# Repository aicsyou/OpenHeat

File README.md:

# OpenHeat：开源智能加热台
* 基于[peng-zhihui](https://github.com/peng-zhihui)的[OpenHeat](https://github.com/peng-zhihui/OpenHeat)， 调整了元器件的封装，方便手工焊接
* 项目设计使用KiCAD软件
* 固件不完全兼容（未完成）
* 注意： PCBA测试中

---------------------------------------------------------------------------

> 用于PCB回流焊的实用加热台，比较炫酷，可能目前市面上 **颜值最高** & **功能最强** 的加热台。

**参数：** 硬件方面基于`ESP32PICO-D4`芯片，输入电源`24V/10A`，最大功率200W，加热温度最高300℃；带蓝牙功能，***后续有空的话我会开发手机APP用于设置升温曲线*** 。

## 21-9-17 修复说明：

---

## 关于本项目

* 本项目参考了 [createskyblue](https://gitee.com/createskyblue) / [OpenT12](https://gitee.com/createskyblue/OpenT12)开源T12电烙铁项目的固件，感谢这位同学设计的优秀交互动画体验，UI设计深得我心哈哈~

* 另外铝基板热床的设计采用了[MRobot-Origin](https://github.com/MRobot-Origin)/ [GS_Hbed](https://github.com/MRobot-Origin/GS_Hbed)同学的分型曲线设计，非常有创意~

## 使用说明

#### 1. 打样说明

直接用Hardware文件夹里的Gerber文件打样即可：主控制器为4层PCB，无特殊工艺要求；热床为铝基板PCB，可以在嘉立创打样。

> 铝基板是一种专门用来散热的PCB板材，大家看到的很多大功率LED灯珠就是这种，前阵子嘉立创开放了铝基板打样业务，还很便宜。所以相比于设计一个金属块做热床，这种方式不但成本低而且美观实用。

另外其实还有一块可选两层板作为固定件的，这个我还没来得及设计，也很简单，大家可以根据自己情况画一个，或者直接3D打印结构件固定也行。

#### 2. 固件说明

固件我这边是基于PlatformIO移植的，所以大家用这个平台的话直接打开下载就行了；如果是用Arduino IDE的话，先安装Library里面的库文件，然后一样下载。

固件库没有完全配置完成（因为原版固件是设计为电烙铁使用的），晚些我硬件都就位了会调试好固件供大家直接下载。

#### 3. 关于结构件

这个我也还在设计，我的风格肯定是以美观小巧为主，大家可以等我放出3D打印文件。

#### 4. 关于温度传感器

我这边是用的是K型热电偶，在PCB上已经集成了采集芯片，需要自己买一个表贴式的K型热电偶连接到板子下方的两个焊盘。

> 注意热电偶和热床的接触要绝缘，用高温胶带隔一下就行。另外热电偶是有极性的，如果发现加热后温度反而下降说明接反了。
>
> 现在代码中还没有加热电偶的代码，晚一点有空了会调好完整固件。大家自己添加也很容易，MAX6675使用SPI驱动，Arduino平台有很多例程。

#### 5. 关于元器件BOM

**注意！！！** C9电容一定要选耐压足够的，因为是并联到24V的VCC上，如果耐压不够短路的话可以看到烟花！！

#### 接线图

## 欢迎star支持 :D

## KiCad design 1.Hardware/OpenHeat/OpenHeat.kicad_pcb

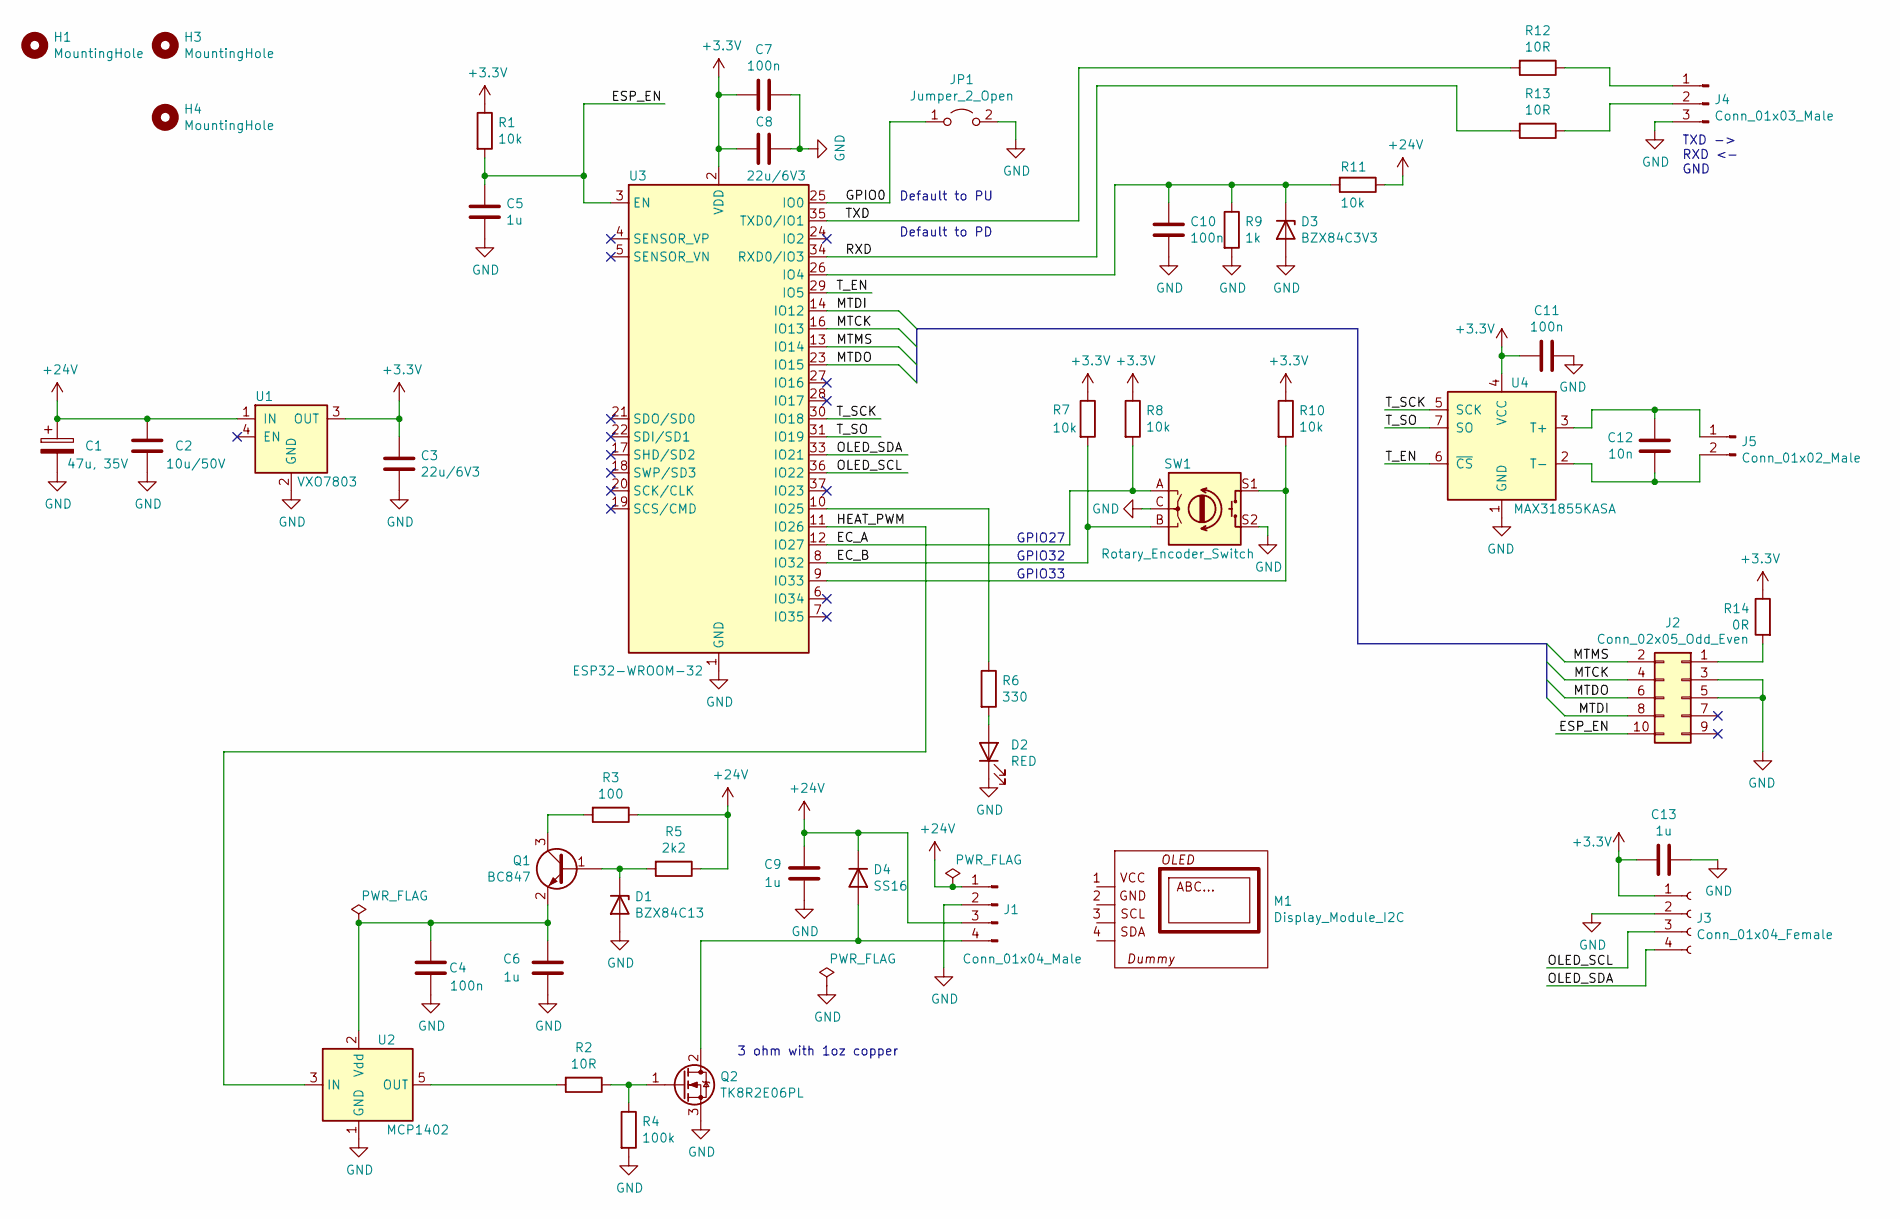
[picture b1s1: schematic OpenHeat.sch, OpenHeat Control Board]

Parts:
C1: 47u, 35V; CP_Radial_D5.0mm_P2.00mm; PartNo 860020472006
C2: 10u/50V; C_1206_3216Metric_Pad1.33x1.80mm_HandSolder
C3, C8: 22u/6V3; C_0805_2012Metric_Pad1.18x1.45mm_HandSolder
C4, C7, C10, C11: 100n; C_0603_1608Metric_Pad1.08x0.95mm_HandSolder
C5, C6, C13: 1u; C_0603_1608Metric_Pad1.08x0.95mm_HandSolder
C9: 1u; C_Rect_L7.2mm_W4.5mm_P5.00mm_FKS2_FKP2_MKS2_MKP2; PartNo B32529C105J
C12: 10n; C_0603_1608Metric_Pad1.08x0.95mm_HandSolder
D1: BZX84C13; D_SOT-23_ANK
D2: RED; LED_0805_2012Metric_Pad1.15x1.40mm_HandSolder
D3: BZX84C3V3; D_SOT-23_ANK
D4: SS16; D_SMA; PartNo SS16_R1_00001
H1, H3, H4: MountingHole; MountingHole_3.2mm_M3
J1: Conn_01x04_Male; TerminalBlock_Phoenix_MKDS-1,5-4-5.08_1x04_P5.08mm_Horizont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
J2: Conn_02x05_Odd_Even; PinHeader_2x05_P1.27mm_Vertical_SMD
J3: Conn_01x04_Female; PinSocket_1x04_P2.54mm_Vertical
J4: Conn_01x03_Male; PinHeader_1x03_P2.54mm_Vertical
J5: Conn_01x02_Male; PinHeader_1x02_P2.54mm_Horizontal
JP1: Jumper_2_Open; PinHeader_1x02_P2.54mm_Vertical
M1: Display_Module_I2C; OLED_128x64_096_I2C
Q1: BC847; SOT-23
Q2: TK8R2E06PL; TO-220-3_Horizontal_TabDown
R1, R7, R8, R10, R11: 10k; R_0603_1608Metric_Pad0.98x0.95mm_HandSolder
R2, R12, R13: 10R; R_0603_1608Metric_Pad0.98x0.95mm_HandSolder
R3: 100; R_0805_2012Metric_Pad1.20x1.40mm_HandSolder
R4: 100k; R_0603_1608Metric_Pad0.98x0.95mm_HandSolder
R5: 2k2; R_0603_1608Metric_Pad0.98x0.95mm_HandSolder
R6: 330; R_0603_1608Metric_Pad0.98x0.95mm_HandSolder
R9: 1k; R_0603_1608Metric_Pad0.98x0.95mm_HandSolder
R14: 0R; R_0603_1608Metric_Pad0.98x0.95mm_HandSolder
SW1: Rotary_Encoder_Switch; RotaryEncoder_Alps_EC11E-Switch_Vertical_H20mm
U1: VXO7803; VXO78-500-M; PartNo VXO7803-500-M-TR
U2: MCP1402; SOT-23-5
U3: ESP32-WROOM-32
U4: MAX31855KASA; SOIC-8_3.9x4.9mm_P1.27mm

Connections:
+3V3: C3.1, C7.1, C8.2, C11.1, C13.2, J3.1, R1.1, R7.1, R8.1, R10.1, R14.1, U1.3 (OUT), U3.2 (VDD), U4.4 (VCC)
+24V: C1.1, C2.1, C9.2, D4.1 (K), J1.1, J1.3, R3.1, R5.1, R11.1, U1.1 (IN)
/EC_A: R8.2, SW1.A, U3.12 (IO27)
/EC_B: R7.2, SW1.B, U3.8 (IO32)
/ESP_EN: C5.1, J2.10, R1.2, U3.3 (EN)
/GPIO0: JP1.1 (A), U3.25 (IO0)
/HEAT_PWM: U2.3 (IN), U3.11 (IO26)
/MTCK: J2.4, U3.16 (IO13)
/MTDI: J2.8, U3.14 (IO12)
/MTDO: J2.6, U3.23 (IO15)
/MTMS: J2.2, U3.13 (IO14)
/OLED_SCL: J3.3, U3.36 (IO22)
/OLED_SDA: J3.4, U3.33 (IO21)
/RXD: R13.2, U3.34 (RXD0/IO3)
/TXD: R12.2, U3.35 (TXD0/IO1)
/T_EN: U3.29 (IO5), U4.6 (~CS~)
/T_SCK: U3.30 (IO18), U4.5 (SCK)
/T_SO: U3.31 (IO19), U4.7 (SO)
GND: C1.2, C2.2, C3.2, C4.2, C5.2, C6.2, C7.2, C8.1, C9.1, C10.2, C11.2, C13.1, D1.2 (A), D2.1 (K), D3.2 (A), J1.2, J2.3, J2.5, J3.2, J4.3, JP1.2 (B), Q2.3 (S), R4.2, R9.2, SW1.C, SW1.S2, U1.2 (GND), U2.1 (GND), U2.4 (GND), U3.1 (GND), U3.15 (GND), U3.38 (GND), U3.39 (GND), U4.1 (GND)
unnamed: C4.1, C6.1, Q1.2 (E), U2.2 (Vdd)
unnamed: C10.1, D3.1 (K), R9.1, R11.2, U3.26 (IO4)
unnamed: C12.1, J5.2, U4.2 (T-)
unnamed: C12.2, J5.1, U4.3 (T+)
unnamed: D1.1 (K), Q1.1 (B), R5.2
unnamed: D2.2 (A), R6.2
unnamed: D4.2 (A), J1.4, Q2.2 (D)
unnamed: J2.1, R14.2
unnamed: J4.1, R12.1
unnamed: J4.2, R13.1
unnamed: Q1.3 (C), R3.2
unnamed: Q2.1 (G), R2.1, R4.1
unnamed: R2.2, U2.5 (OUT)
unnamed: R6.1, U3.10 (IO25)
unnamed: R10.2, SW1.S1, U3.9 (IO33)

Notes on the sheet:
Default to PD
Default to PU
GPIO32
GPIO27
GPIO33
3 ohm with 1oz copper
TXD -> RXD <- GND

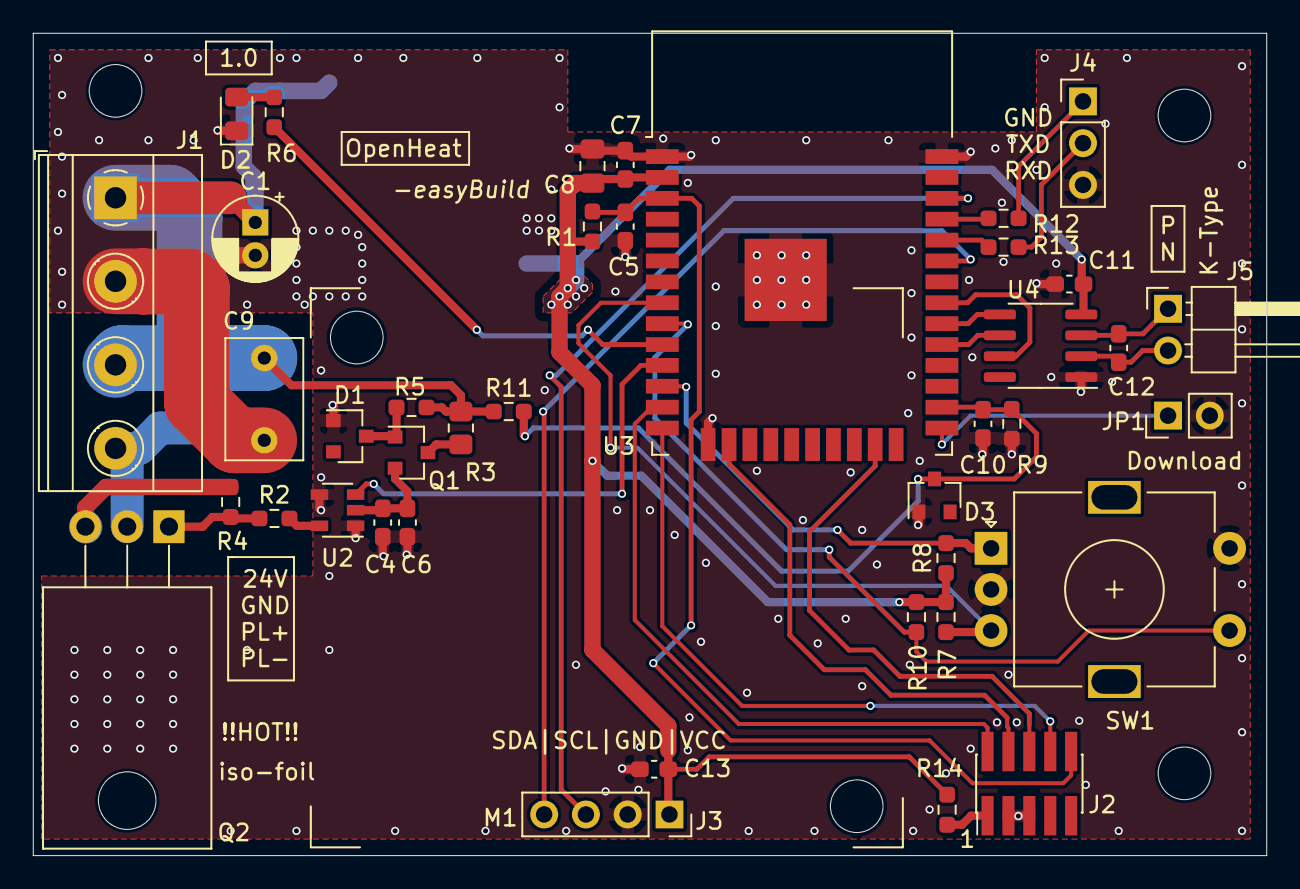
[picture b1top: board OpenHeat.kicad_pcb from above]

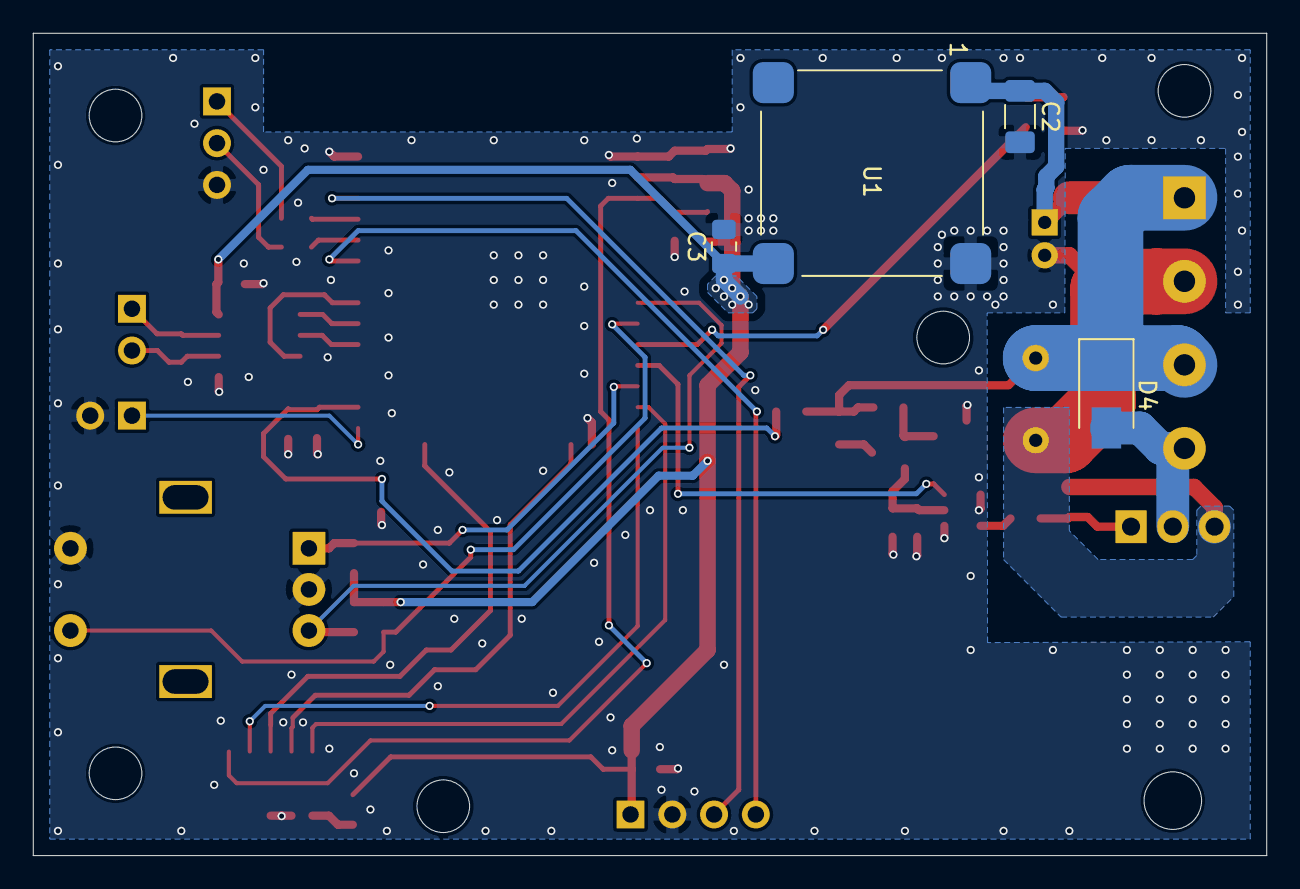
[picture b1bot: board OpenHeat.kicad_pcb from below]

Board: 2 copper layers, 75.0 x 50.0 mm, 48 parts (4 on the bottom side), 34 nets.

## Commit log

2021-10-18 KiCAD project
    Controller modified for easier build, project created with KiCAD
2021-10-18 Update images
2021-10-19 Update OpenHeat.kicad_pcb
    Additional VIAs added
2021-10-19 Add manufacturing data for controller PCB
    Gerber files and drill files
